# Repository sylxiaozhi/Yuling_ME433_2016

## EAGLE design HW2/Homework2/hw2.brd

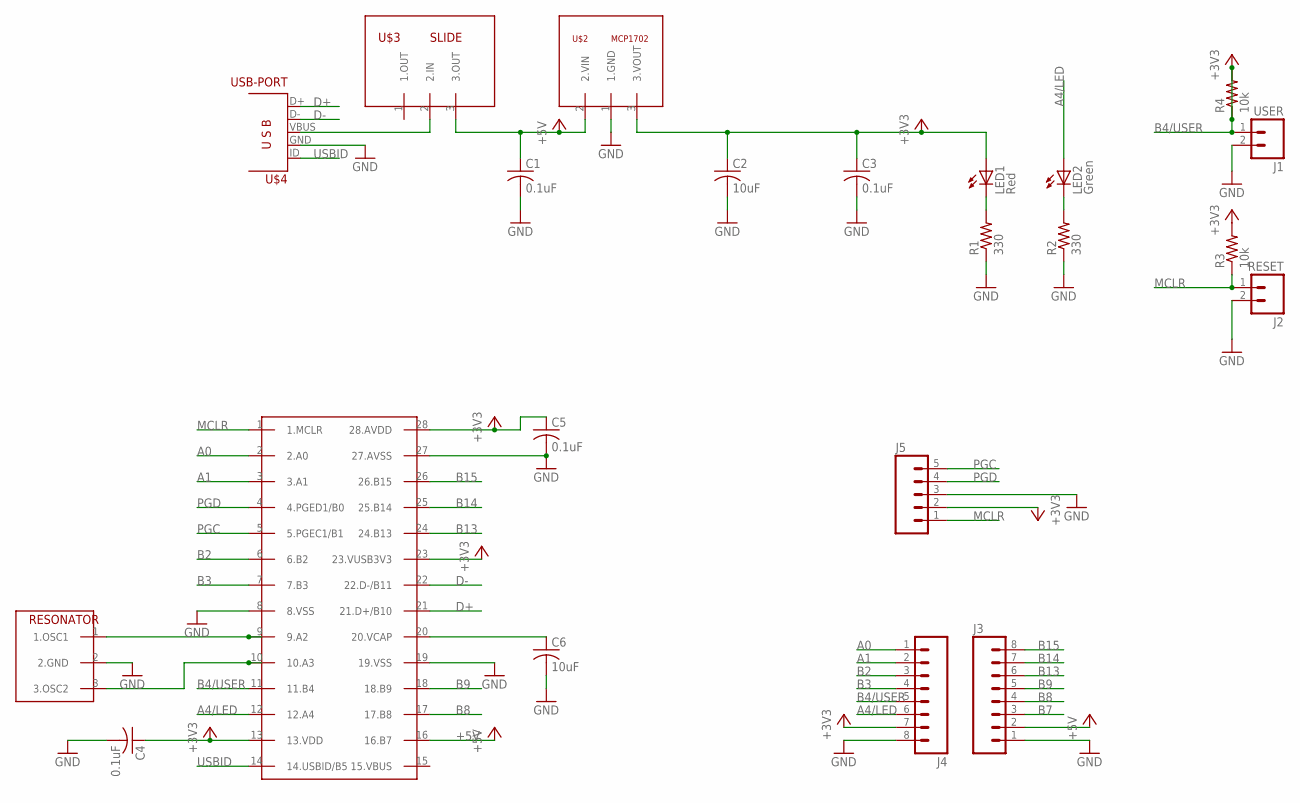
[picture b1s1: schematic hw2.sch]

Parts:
C1, C3, C4, C5: 0.1uF; C025-024X044
C2, C6: 10uF; C025-024X044
J1: USER; JST-2-PTH-NS
J2: RESET; JST-2-PTH-NS
J3, J4: M08; 1X08_ROUND
J5: M05PTH; 1X05
LED1: Red; LED3MM
LED2: Green; LED3MM
R1, R2: 330; 0204/5
R3, R4: 10k; 0204/5
U$1: PIC; DIL28-3
U$2: MCP1702; TO92
U$3: SLIDE; MOLEX-1X3
U$4: USB-PORT; USB-MB-H
U$5: RESONATOR; MOLEX-1X3

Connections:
+3V3: C2.1, C3.1, C4.1, C5.1, J4.7, J5.2, LED1.A, R3.2, U$1.13 (13.VDD), U$1.23 (23.VUSB3V3), U$1.28 (28.AVDD), U$2.3 (3.VOUT)
+5V: C1.1, J3.2, U$1.16 (16.B7), U$2.2 (2.VIN), U$3.3 (3.OUT)
A0: J4.1, U$1.2 (2.A0)
A1: J4.2, U$1.3 (3.A1)
A4/LED: J4.6, LED2.A, U$1.12 (12.A4)
B2: J4.3, U$1.6 (6.B2)
B3: J4.4, U$1.7 (7.B3)
B4/USER: J1.1, J4.5, R4.1, R4.2, U$1.11 (11.B4)
B7: J3.3
B8: J3.4, U$1.17 (17.B8)
B9: J3.5, U$1.18 (18.B9)
B13: J3.6, U$1.24 (24.B13)
B14: J3.7, U$1.25 (25.B14)
B15: J3.8, U$1.26 (26.B15)
D+: U$1.21 (21.D+/B10), U$4.D+
D-: U$1.22 (22.D-/B11), U$4.D-
GND: C1.2, C2.2, C3.2, C4.2, C5.2, C6.2, J1.2, J2.2, J3.1, J4.8, J5.3, R1.1, R2.1, U$1.8 (8.VSS), U$1.19 (19.VSS), U$1.27 (27.AVSS), U$2.1 (1.GND), U$4.GND, U$5.2 (2.GND)
MCLR: J2.1, J5.1, R3.1, U$1.1 (1.MCLR)
unnamed: U$1.9 (9.A2), U$5.1 (1.OSC1)
unnamed: U$1.10 (10.A3), U$5.3 (3.OSC2)
unnamed: C6.1, U$1.20 (20.VCAP)
unnamed: U$3.2 (2.IN), U$4.VBUS
unnamed: LED1.K (C), R1.2
unnamed: LED2.K (C), R2.2
PGC: J5.5, U$1.5 (5.PGEC1/B1)
PGD: J5.4, U$1.4 (4.PGED1/B0)
USBID: U$1.14 (14.USBID/B5), U$4.ID

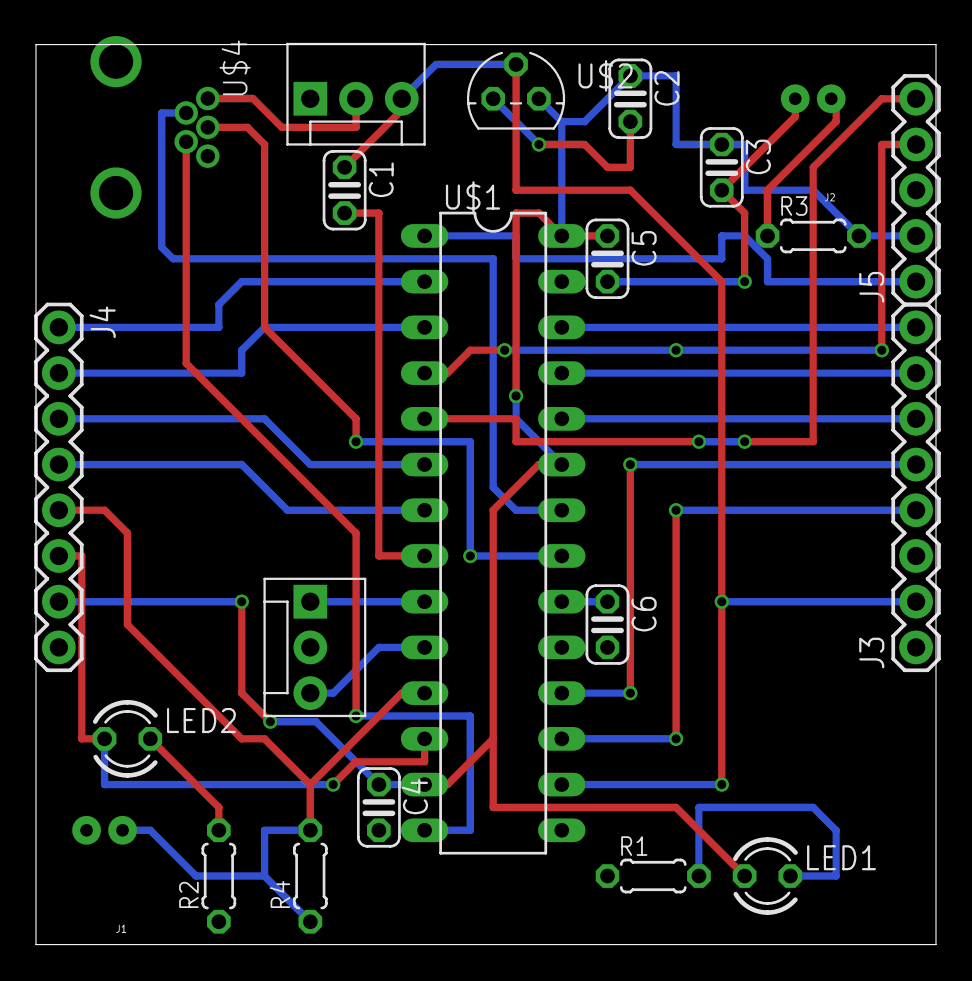
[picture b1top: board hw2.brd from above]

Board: 2 copper layers, 50.0 x 50.0 mm, 22 parts (0 on the bottom side), 26 nets.

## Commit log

2016-04-05 First commit.
2016-04-05 test
2016-04-05 Create HW1
2016-04-05 sample code
2016-04-05 pragmas filled
2016-04-05 A4 and B4 registered.
2016-04-05 Final Code
2016-04-05 Homework 1 Pictures
2016-04-06 Move position
2016-04-06 Format
2016-04-13 library
2016-04-13 schematic
2016-04-14 board
2016-04-14 Ready to be checked before order #I don’t really trust my design…so may I just use yours?
2016-04-14 Ready to be checked before order #I don’t really trust my design though. May I just use yours?
2016-04-14 Final Commit
2016-04-14 Final_Final_commit
2016-04-14 Final_Final_Final_Commit
2016-04-18 Create HW3
2016-04-21 edit
2016-04-25 I2C copy
2016-05-16 android hello world done
2016-05-22 done 3D print
2016-05-23 formatting
2016-06-08 final commit of the course
